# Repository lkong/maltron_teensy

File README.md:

# maltron_teensy
Alternative Maltron keyboard controller with Teensy 2.0++.
Compatible with QMK firmware.

Order the board directly from OSHPark:
<a href="https://oshpark.com/shared_projects/BtYDxEX8"></img></a>

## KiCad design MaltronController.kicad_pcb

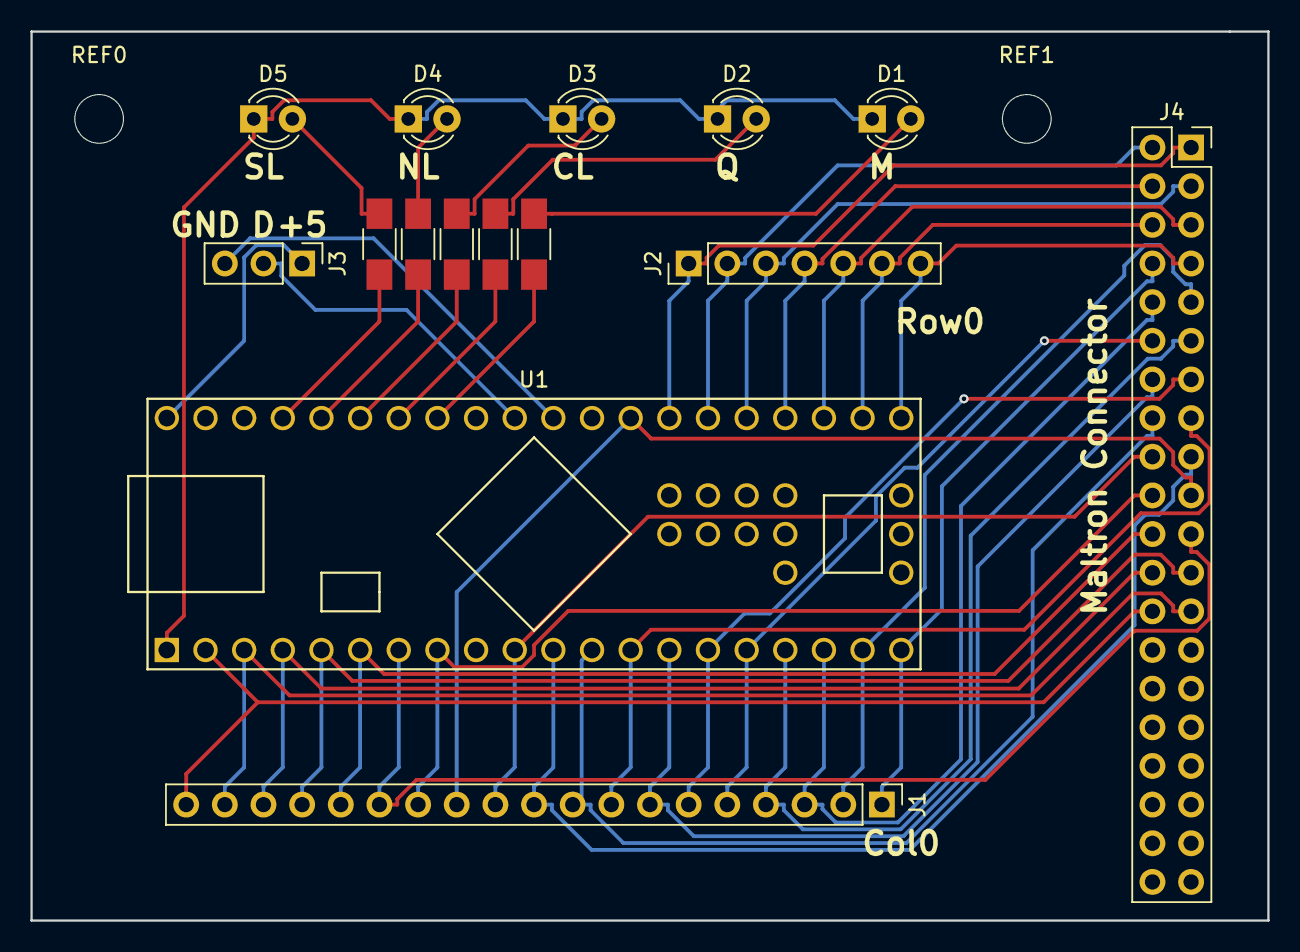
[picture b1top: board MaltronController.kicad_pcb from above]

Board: 2 copper layers, 81.3 x 58.4 mm, 12 parts (0 on the bottom side), 30 nets.

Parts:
D1, D2, D3, D4, D5: LED; LED_D3.0mm
J1: CONN_COL; Socket_Strip_Straight_1x19_Pitch2.54mm
J2: CONN_ROW; Socket_Strip_Straight_1x07_Pitch2.54mm
J3: RGB_LED; Socket_Strip_Straight_1x03_Pitch2.54mm
J4: CONN_MALTRON; Socket_Strip_Straight_2x20_Pitch2.54mm
REF0, REF1: MountingHole; MountingHole_3.2mm_M3
U1: Teensy++2.0; Teensy2.0++

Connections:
unnamed: D1.1, D2.1, D3.1, D4.1, D5.1, U1.1
unnamed: J1.1, J4.8, U1.20
unnamed: J1.2, J4.9, U1.19
unnamed: J1.3, J4.10, U1.18
unnamed: J1.4, J4.11, U1.17
unnamed: J1.5, J4.12, U1.16
unnamed: J1.6, J4.13, U1.15
unnamed: J1.7, J4.14, U1.14
unnamed: J1.8, J4.15, U1.13
unnamed: J1.9, J4.16, U1.12
unnamed: J1.10, J4.17, U1.11
unnamed: J1.11, J4.18, U1.10
unnamed: J1.12, J4.19, U1.31
unnamed: J1.13, J4.20, U1.8
unnamed: J1.14, J4.21, U1.7
unnamed: J1.15, J4.22, U1.6
unnamed: J1.16, J4.23, U1.5
unnamed: J1.17, J4.24, U1.4
unnamed: J1.18, J4.25, U1.3
unnamed: J1.19, J4.26, U1.2
unnamed: J2.1, J4.1, U1.30
unnamed: J2.2, J4.2, U1.29
unnamed: J2.3, J4.3, U1.28
unnamed: J2.4, J4.4, U1.27
unnamed: J2.5, J4.5, U1.26
unnamed: J2.6, J4.6, U1.25
unnamed: J2.7, J4.7, U1.24
unnamed: J3.1, U1.43
unnamed: J3.2, U1.34
unnamed: J3.3, U1.33

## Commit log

2017-12-09 init
